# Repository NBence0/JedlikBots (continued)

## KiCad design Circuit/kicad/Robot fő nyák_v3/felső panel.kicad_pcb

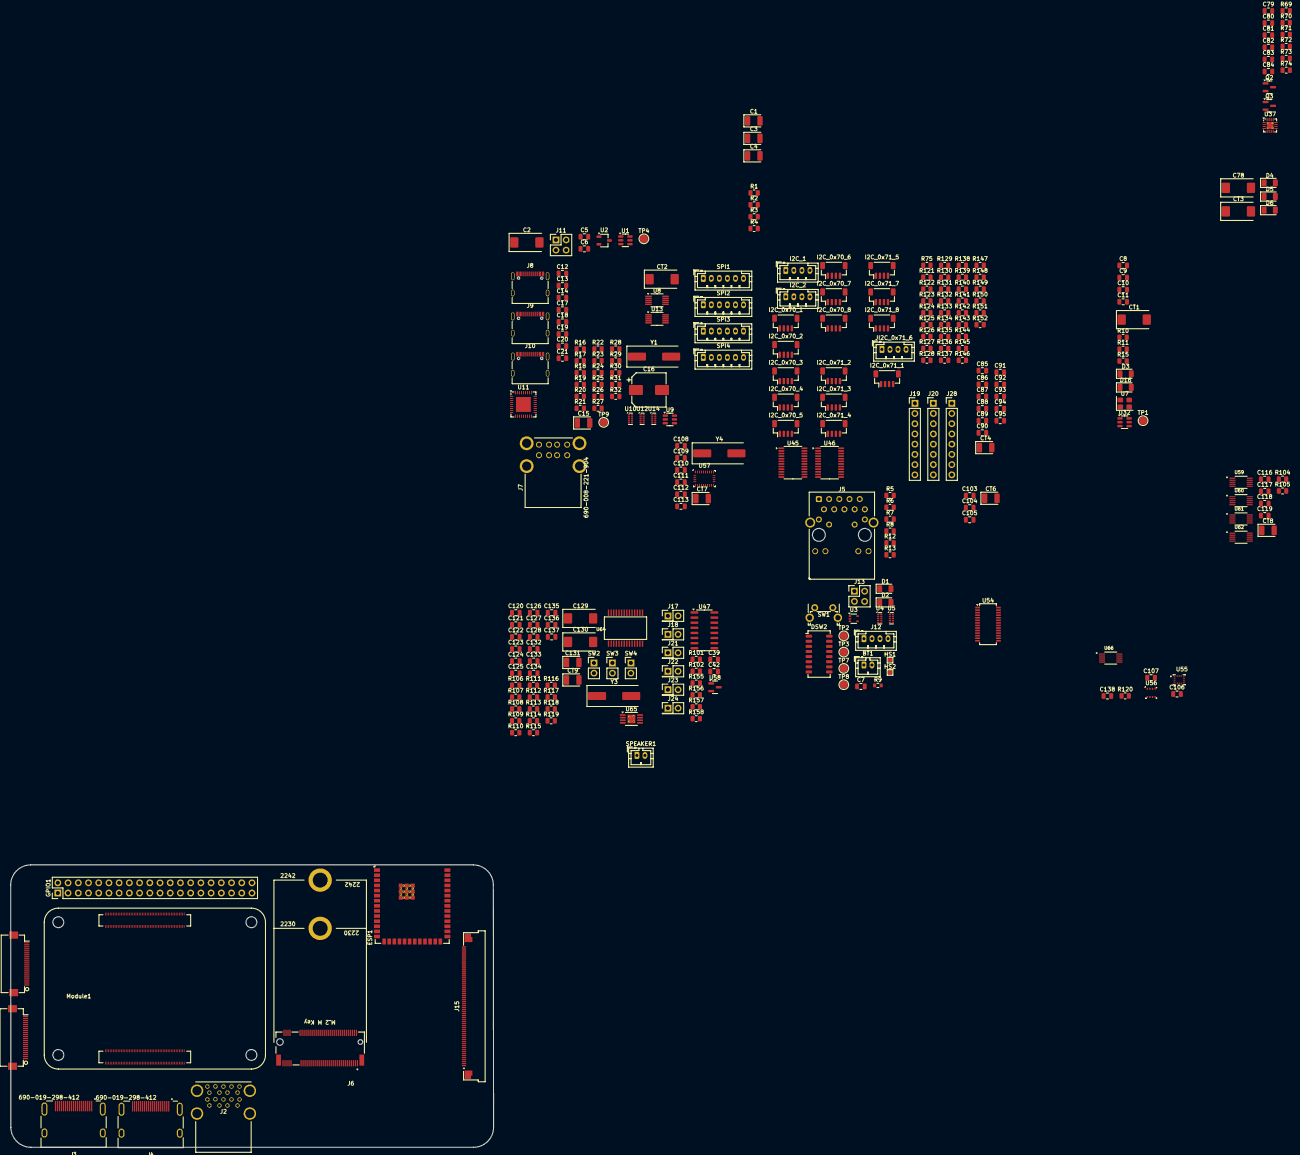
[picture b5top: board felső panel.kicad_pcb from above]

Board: 6 copper layers, 120.0 x 70.2 mm, 283 parts (0 on the bottom side), 343 nets, no tracks yet.

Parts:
BT1: Battery_Cell; JST_PH_B2B-PH-K_1x02_P2.00mm_Vertical
C1, C3, C4, C15: 10u; CP_EIA-3528-21_Kemet-B
C2: 100uF; CP_EIA-7343-31_Kemet-D
C5, C6, C7, C11: 100n; C_0805_2012Metric
C8, C9, C10, C17, C18, C19, C20, C21, C80, C81, C82, C83, C85, C86, C87, C88, C89, C90, C91, C92, C93, C94, C95, C103, C104, C105, C106, C107, C110, C111, C116, C117, C118, C119, C121, C124, C125, C127, C128, C132, C133, C134, C135, C136, C138: 1uf; C_0805_2012Metric
C12, C14, C120, C122: 22pf; C_0805_2012Metric
C13, C42, C79, C84: 100nf; C_0805_2012Metric
C16: 470uF; CP_Elec_8x10
C39: 68pf; C_0805_2012Metric
C78, C129, C130: 100uf; CP_EIA-7343-31_Kemet-D
C108, C109: 0.1uF; C_0805_2012Metric
C112, C113: 22pF; C_0805_2012Metric
C123, C126, C137: 0.022-μF; C_0805_2012Metric
C131: 10uf; CP_EIA-3528-21_Kemet-B
CT1, CT2, CT3: 100uf; CP_EIA-7343-31_Kemet-D
CT4, CT6, CT7, CT8, CT9: 10uf; CP_EIA-3528-21_Kemet-B
D1, D3: LED Green; D_1206_3216Metric
D2: LED Red; D_1206_3216Metric
D4, D5, D6, D16: LED; D_1206_3216Metric
DSI1, DSI2: Conn_01x22_Female; Hirose_FH12-22S-0.5SH_1x22-1MP_P0.50mm_Horizontal
DSW2: SW_DIP_x08; SW_DIP_SPSTx08_Slide_Copal_CHS-08A_W5.08mm_P1.27mm_JPin
ESP1: ESP32-S3-WROOM-2
GPIO1: THD-20-R; PinHeader_2x20_P2.54mm_Vertical
HS1, HS2: Heatsink; TestPoint_Pad_1.0x1.0mm
I2C_0x70_1, I2C_0x70_2, I2C_0x70_3, I2C_0x70_4, I2C_0x70_5, I2C_0x70_6, I2C_0x70_7, I2C_0x70_8, I2C_0x71_1, I2C_0x71_2, I2C_0x71_3, I2C_0x71_4, I2C_0x71_5, I2C_0x71_7, I2C_0x71_8: Conn_01x04_Pin; JST_SH_BM04B-SRSS-TB_1x04-1MP_P1.00mm_Vertical
I2C_1, I2C_2: Conn_01x04_Pin; JST_PH_B4B-PH-K_1x04_P2.00mm_Vertical
J2: USB3_A; MTCONN_UBAF30-D2011
J3, J4: 690-019-298-412; EDAC 690-019-298-412
J5: MagJack-A70-112-331N126; TRJG0926HENL
J6: Bus_M.2_Socket_M; M.2 M Key socket
J7: 690-008-221-904; MOLEX_USB_67298-4090
J8, J9, J10: USB_C_Receptacle_USB2.0_16P; USB_C_Receptacle_Palconn_UTC16-G
J11, J13: THD-02-R; PinHeader_2x02_P2.54mm_Vertical
J12: Conn_01x04_Socket; JST_PH_B4B-PH-K_1x04_P2.00mm_Vertical
J15: Conn_01x60_MountingPin; Amphenol_F32Q-1A7x1-11060_1x60-1MP_P0.5mm_Horizontal
J17, J18, J21, J22, J23, J24: Conn_01x02_Pin; PinHeader_2x01_P2.54mm_Vertical
J19, J20, J28: Conn_01x08_Pin; PinHeader_1x08_P2.54mm_Vertical
JI2C_0x71_6: Conn_01x04_Pin; JST_PH_B4B-PH-K_1x04_P2.00mm_Vertical
Module1: ComputeModule5-CM5; Raspberry-Pi-5-Compute-Module
Q2, Q3: bc akármi; SOT-23
R1, R26: 15K 1%; R_0805_2012Metric
R2, R3, R4, R16, R17, R27, R28, R121, R122, R123, R124, R125, R126, R127, R128, R129, R130, R131, R132, R133, R134, R135, R136, R137, R138, R139, R140, R141, R142, R143, R144, R145, R146, R147, R148, R149, R150, R151, R152: 2.2K 1%; R_0805_2012Metric
R5, R6, R7: 4.7k; R_0805_2012Metric
R8, R15, R69, R70, R71: 1k; R_0805_2012Metric
R9: 1k; R_0603_1608Metric
R10, R18, R72, R73, R74, R75, R101, R102, R155, R156, R157, R158: 10k; R_0805_2012Metric
R11: 100; R_0805_2012Metric
R12, R13: 470R; R_0805_2012Metric
R19, R20, R21, R25: 36K 1%; R_0805_2012Metric
R22: 12K 1%; R_0805_2012Metric
R23, R24, R29, R30, R31, R32: 5.1K 1%; R_0805_2012Metric
R104, R105, R120: 47k; R_0805_2012Metric
R106, R107: 1.5-kΩ; R_0805_2012Metric
R108: 22; R_0805_2012Metric
R109: 22Ω; R_0805_2012Metric
R110: 1M; R_0805_2012Metric
R111, R112: 16; R_0805_2012Metric
R113, R114: 330; R_0805_2012Metric
R115, R116, R117, R118, R119: 10K; R_0805_2012Metric
SPEAKER1: Conn_01x02_Pin; JST_PH_B2B-PH-K_1x02_P2.00mm_Vertical
SPI1, SPI2, SPI3, SPI4: Conn_01x06_Socket; JST_PH_B6B-PH-K_1x06_P2.00mm_Vertical
SW1: Right angle Tact button; SW_Tactile_SPST_Angled_PTS645Vx58-2LFS
SW2, SW3, SW4: SW_Push; PinHeader_1x02_P2.54mm_Vertical
TP1, TP2, TP3, TP4, TP7, TP8, TP9: TestPoint; TestPoint_Pad_D2.0mm
U1, U9: AP22653W6; SOT-23-6
U2: RT9742SNGV; TSOT-23
U3: 74LVC1G07SE-7; SOT-353_SC-70-5
U4, U5, U10, U12, U14: TPD4EUSB30; USON-10_2.5x1.0mm_P0.5mm
U7: ASEK-32.768KHZ-L-R-T; Crystal_SMD_3225-4Pin_3.2x2.5mm
U8, U13: FSUSB42MUX; MSOP-10_3x3mm_P0.5mm
U11: USB2514B-I/M2; QFN-36-1EP_6x6mm_P0.5mm_EP3.7x3.7mm
U32: AP22815AWU; SOT-23-6
U37: CH343P; QFN-16-1EP_3x3mm_P0.5mm_EP1.7x1.7mm_ThermalVias
U45, U46: TCA9548APWR; TSSOP-24_4.4x7.8mm_P0.65mm
U47: MCP3208; SOIC-16_3.9x9.9mm_P1.27mm
U54: MCP23S17_SO; SSOP-28_3.9x9.9mm_P0.635mm
U55: ICM-45686; IC_ICM-45686
U56: BME280; Bosch_LGA-8_2.5x2.5mm_P0.65mm_ClockwisePinNumbering
U57: BNO080; LGA-28_5.2x3.8mm_P0.5mm
U58: MCP1541-TT; SOT-23
U59, U60, U61, U62, U66: TS5A23157DGSR; SOP50P490X110-10N
U64: PCM2704CDBR; SSOP28
U65: TPA6203A1DGN; MSOP-8-1EP_3x3mm_P0.65mm_EP1.95x2.15mm_ThermalVias
Y1: 24MHz; Crystal_SMD_HC49-SD
Y3: 5MHz; Crystal_SMD_HC49-SD
Y4: 32.768MHz; Crystal_SMD_HC49-SD

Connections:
1.8V: J20.7, J20.8, Module1.88 (+1.8v_(Output)), Module1.90 (+1.8v_(Output)), TP8.1
3V3_M.2: GPIO1.1, GPIO1.17, J15.38, J15.39, J15.40, J15.41, J15.42, J15.43, R10.1, R11.1, U32.6 (IN)
5V1: C1.1, C5.1, C15.1, C121.2, C134.1, C135.1, C136.1, CT9.1, J15.55, J15.56, U1.1 (IN), U2.1 (IN), U9.1 (IN), U64.10 (VBUS), U65.6 (V_{DD})
/CM5_GPIO ( Ethernet, GPIO, SDCARD)/+3.3v: D1.2 (A), D2.2 (A), DSI1.22, DSI2.22, J5.15 (LEDY_A), J5.17 (LEDG_A), Module1.78 (GPIO_VREF(1.8v/3.3v_Input)), Module1.84 (+3.3v_(Output)), Module1.86 (+3.3v_(Output)), R2.1, TP7.1, U3.5 (VCC)
/CM5_GPIO ( Ethernet, GPIO, SDCARD)/CAM_GPIO0: DSI1.17, Module1.97 (CAM_GPIO0)
/CM5_GPIO ( Ethernet, GPIO, SDCARD)/CAM_GPIO1: DSI1.18, Module1.100 (CAM_GPIO1)
/CM5_GPIO ( Ethernet, GPIO, SDCARD)/ETH_LEDG: Module1.17 (Ethernet_nLED2(3.3v)), R12.2
/CM5_GPIO ( Ethernet, GPIO, SDCARD)/ETH_LEDY: Module1.15 (Ethernet_nLED3(3.3v)), R13.2
/CM5_GPIO ( Ethernet, GPIO, SDCARD)/GPIO2: GPIO1.3, Module1.58 (GPIO2)
/CM5_GPIO ( Ethernet, GPIO, SDCARD)/GPIO3: GPIO1.5, Module1.56 (GPIO3)
/CM5_GPIO ( Ethernet, GPIO, SDCARD)/GPIO12: GPIO1.32, Module1.31 (GPIO12)
/CM5_GPIO ( Ethernet, GPIO, SDCARD)/GPIO13: GPIO1.33, Module1.28 (GPIO13)
/CM5_GPIO ( Ethernet, GPIO, SDCARD)/GPIO16: GPIO1.36, Module1.29 (GPIO16)
/CM5_GPIO ( Ethernet, GPIO, SDCARD)/GPIO17: GPIO1.11, Module1.50 (GPIO17)
/CM5_GPIO ( Ethernet, GPIO, SDCARD)/GPIO18: GPIO1.12, Module1.49 (GPIO18)
/CM5_GPIO ( Ethernet, GPIO, SDCARD)/GPIO22: GPIO1.15, Module1.46 (GPIO22)
/CM5_GPIO ( Ethernet, GPIO, SDCARD)/GPIO23: GPIO1.16, Module1.47 (GPIO23)
/CM5_GPIO ( Ethernet, GPIO, SDCARD)/GPIO24: GPIO1.18, Module1.45 (GPIO24)
/CM5_GPIO ( Ethernet, GPIO, SDCARD)/GPIO25: GPIO1.22, Module1.41 (GPIO25)
/CM5_GPIO ( Ethernet, GPIO, SDCARD)/GPIO26: GPIO1.37, Module1.24 (GPIO26)
/CM5_GPIO ( Ethernet, GPIO, SDCARD)/GPIO27: GPIO1.13, Module1.48 (GPIO27)
/CM5_GPIO ( Ethernet, GPIO, SDCARD)/ID_SC: GPIO1.28, J11.1, Module1.35 (ID_SC)
/CM5_GPIO ( Ethernet, GPIO, SDCARD)/ID_SD: GPIO1.27, J11.3, Module1.36 (ID_SD)
/CM5_GPIO ( Ethernet, GPIO, SDCARD)/PWM: J12.2, Module1.19 (FAN_PWM)
/CM5_GPIO ( Ethernet, GPIO, SDCARD)/PWR_BUT: Module1.92 (PWR_BUT), SW1.1
/CM5_GPIO ( Ethernet, GPIO, SDCARD)/SYNC_OUT: Module1.18 (Ethernet_SYNC_OUT(3.3v)), TP2.1
/CM5_GPIO ( Ethernet, GPIO, SDCARD)/TACHO: J12.4, Module1.16 (FAN_TACHO)
/CM5_GPIO ( Ethernet, GPIO, SDCARD)/TR0_TAP: J5.11 (VC1), J13.3
/CM5_GPIO ( Ethernet, GPIO, SDCARD)/TR1_TAP: J5.12 (VC2), J13.1
/CM5_GPIO ( Ethernet, GPIO, SDCARD)/TR2_TAP: J5.13 (VC3), J13.2
/CM5_GPIO ( Ethernet, GPIO, SDCARD)/TR3_TAP: J5.14 (VC4), J13.4
/CM5_GPIO ( Ethernet, GPIO, SDCARD)/TRD0_N: J5.2 (TRD0-), Module1.10 (Ethernet_Pair0_N), U5.4 (D2+), U5.7
/CM5_GPIO ( Ethernet, GPIO, SDCARD)/TRD0_P: J5.1 (TRD0+), Module1.12 (Ethernet_Pair0_P), U5.5 (D2-), U5.6
/CM5_GPIO ( Ethernet, GPIO, SDCARD)/TRD1_N: J5.6 (TRD1-), Module1.6 (Ethernet_Pair1_N), U5.2 (D1-), U5.9
/CM5_GPIO ( Ethernet, GPIO, SDCARD)/TRD1_P: J5.3 (TRD1+), Module1.4 (Ethernet_Pair1_P), U5.1 (D1+), U5.10
/CM5_GPIO ( Ethernet, GPIO, SDCARD)/TRD2_N: J5.8 (TRD2-), Module1.9 (Ethernet_Pair2_N), U4.4 (D2+), U4.7
/CM5_GPIO ( Ethernet, GPIO, SDCARD)/TRD2_P: J5.7 (TRD2+), Module1.11 (Ethernet_Pair2_P), U4.5 (D2-), U4.6
/CM5_GPIO ( Ethernet, GPIO, SDCARD)/TRD3_N: J5.10 (TRD3-), Module1.5 (Ethernet_Pair3_N), U4.2 (D1-), U4.9
/CM5_GPIO ( Ethernet, GPIO, SDCARD)/TRD3_P: J5.9 (TRD3+), Module1.3 (Ethernet_Pair3_P), U4.1 (D1+), U4.10
/CM5_GPIO ( Ethernet, GPIO, SDCARD)/VBAT: BT1.1 (+), Module1.76 (VBAT)
/CM5_GPIO ( Ethernet, GPIO, SDCARD)/nPWR_LED: Module1.95 (LED_nPWR), U3.2
/CM5_HighSpeed/DPHY0_C_N: DSI1.8, Module1.127 (MIPI0_C_N)
/CM5_HighSpeed/DPHY0_C_P: DSI1.9, Module1.129 (MIPI0_C_P)
/CM5_HighSpeed/DPHY0_D0_N: DSI1.2, Module1.115 (MIPI0_D0_N)
/CM5_HighSpeed/DPHY0_D0_P: DSI1.3, Module1.117 (MIPI0_D0_P)
/CM5_HighSpeed/DPHY0_D1_N: DSI1.5, Module1.121 (MIPI0_D1_N)
/CM5_HighSpeed/DPHY0_D1_P: DSI1.6, Module1.123 (MIPI0_D1_P)
/CM5_HighSpeed/DPHY0_D2_N: DSI1.11, Module1.133 (MIPI0_D2_N)
/CM5_HighSpeed/DPHY0_D2_P: DSI1.12, Module1.135 (MIPI0_D2_P)
/CM5_HighSpeed/DPHY0_D3_N: DSI1.14, Module1.139 (MIPI0_D3_N)
/CM5_HighSpeed/DPHY0_D3_P: DSI1.15, Module1.141 (MIPI0_D3_P)
/CM5_HighSpeed/DPHY1_C_N: DSI2.8, Module1.187 (MIPI1_C_N)
/CM5_HighSpeed/DPHY1_C_P: DSI2.9, Module1.189 (MIPI1_C_P)
/CM5_HighSpeed/DPHY1_D0_N: DSI2.2, Module1.175 (MIPI1_D0_N)
/CM5_HighSpeed/DPHY1_D0_P: DSI2.3, Module1.177 (MIPI1_D0_P)
/CM5_HighSpeed/DPHY1_D1_N: DSI2.5, Module1.181 (MIPI1_D1_N)
/CM5_HighSpeed/DPHY1_D1_P: DSI2.6, Module1.183 (MIPI1_D1_P)
/CM5_HighSpeed/DPHY1_D2_N: DSI2.11, Module1.193 (MIPI1_D2_N)
/CM5_HighSpeed/DPHY1_D2_P: DSI2.12, Module1.195 (MIPI1_D2_P)
/CM5_HighSpeed/DPHY1_D3_N: DSI2.14, Module1.194 (MIPI1_D3_N)
/CM5_HighSpeed/DPHY1_D3_P: DSI2.15, Module1.196 (MIPI1_D3_P)
/CM5_HighSpeed/GPIO_VREF: R3.1, R4.1
/CM5_HighSpeed/HDMI0_CEC: J3.13 (CEC), Module1.151 (HDMI0_CEC)
/CM5_HighSpeed/HDMI0_CK_N: J3.12 (CK-), Module1.190 (HDMI0_CLK_N)
/CM5_HighSpeed/HDMI0_CK_P: J3.10 (CK+), Module1.188 (HDMI0_CLK_P)
/CM5_HighSpeed/HDMI0_D0_N: J3.9 (D0-), Module1.184 (HDMI0_TX0_N)
/CM5_HighSpeed/HDMI0_D0_P: J3.7 (D0+), Module1.182 (HDMI0_TX0_P)
/CM5_HighSpeed/HDMI0_D1_N: J3.6 (D1-), Module1.178 (HDMI0_TX1_N)
/CM5_HighSpeed/HDMI0_D1_P: J3.4 (D1+), Module1.176 (HDMI0_TX1_P)
/CM5_HighSpeed/HDMI0_D2_N: J3.3 (D2-), Module1.172 (HDMI0_TX2_N)
/CM5_HighSpeed/HDMI0_D2_P: J3.1 (D2+), Module1.170 (HDMI0_TX2_P)
/CM5_HighSpeed/HDMI0_HOTPLUG: J3.19 (HPD/HEAC-), Module1.153 (HDMI0_HOTPLUG)
/CM5_HighSpeed/HDMI0_SCL: J3.15 (SCL), Module1.200 (HDMI0_SCL)
/CM5_HighSpeed/HDMI0_SDA: J3.16 (SDA), Module1.199 (HDMI0_SDA)
/CM5_HighSpeed/HDMI1_CEC: J4.13 (CEC), Module1.149 (HDMI1_CEC)
/CM5_HighSpeed/HDMI1_CK_N: J4.12 (CK-), Module1.166 (HDMI1_CLK_N)
/CM5_HighSpeed/HDMI1_CK_P: J4.10 (CK+), Module1.164 (HDMI1_CLK_P)
/CM5_HighSpeed/HDMI1_D0_N: J4.9 (D0-), Module1.160 (HDMI1_TX0_N)
/CM5_HighSpeed/HDMI1_D0_P: J4.7 (D0+), Module1.158 (HDMI1_TX0_P)
/CM5_HighSpeed/HDMI1_D1_N: J4.6 (D1-), Module1.154 (HDMI1_TX1_N)
/CM5_HighSpeed/HDMI1_D1_P: J4.4 (D1+), Module1.152 (HDMI1_TX1_P)
/CM5_HighSpeed/HDMI1_D2_N: J4.3 (D2-), Module1.148 (HDMI1_TX2_N)
/CM5_HighSpeed/HDMI1_D2_P: J4.1 (D2+), Module1.146 (HDMI1_TX2_P)
/CM5_HighSpeed/HDMI1_HOTPLUG: J4.19 (HPD/HEAC-), Module1.143 (HDMI1_HOTPLUG)
/CM5_HighSpeed/HDMI1_SCL: J4.15 (SCL), Module1.147 (HDMI1_SCL)
/CM5_HighSpeed/HDMI1_SDA: J4.16 (SDA), Module1.145 (HDMI1_SDA)
/CM5_HighSpeed/HDMI_5v: C6.1, J3.18 (+5V), J4.18 (+5V), U2.2 (OUT)
/CM5_HighSpeed/PCIE_CLK_N: J6.53 (REFCLKn), Module1.112 (PCIe_CLK_N)
/CM5_HighSpeed/PCIE_CLK_P: J6.55 (REFCLKp), Module1.110 (PCIe_CLK_P)
/CM5_HighSpeed/PCIE_PWR_EN: Module1.106 (PCIE_PWR_EN), U32.4 (EN)
/CM5_HighSpeed/PCIE_RX_N: J6.43 (PETp0), Module1.118 (PCIe_RX_N)
/CM5_HighSpeed/PCIE_RX_P: J6.41 (PETn0), Module1.116 (PCIe_RX_P)
/CM5_HighSpeed/PCIE_TX_N: J6.49 (PERp0), Module1.124 (PCIe_TX_N)
/CM5_HighSpeed/PCIE_TX_P: J6.47 (PERn0), Module1.122 (PCIe_TX_P)
/CM5_HighSpeed/PCIE_nCLKREQ: J6.52 (~CLKREQ), Module1.102 (PCIe_nCLKREQ)
/CM5_HighSpeed/PCIE_nRST: J6.50 (~PERST), Module1.109 (PCIe_nRST)
/CM5_HighSpeed/PCIE_nWAKE: J6.54 (~PEWAKE), Module1.104 (PCIE_nWAKE)
/CM5_HighSpeed/SCL0: DSI1.20, Module1.80 (SCL0)
/CM5_HighSpeed/SCL1: DSI2.20, J11.2, R4.2
/CM5_HighSpeed/SDA0: DSI1.21, Module1.82 (SDA0)
/CM5_HighSpeed/SDA1: DSI2.21, J11.4, R3.2
/CM5_HighSpeed/USB2_N: Module1.103 (USB2_N), U8.4 (D_N)
/CM5_HighSpeed/USB2_P: Module1.105 (USB2_P), U8.3 (D_P)
/CM5_HighSpeed/USB3-0-D_N: J2.A2 (D-), Module1.136 (USB3-0-D_N)
/CM5_HighSpeed/USB3-0-D_P: J2.A3 (D+), Module1.134 (USB3-0-D_P)
/CM5_HighSpeed/USB3-0-RX_N: J2.A6 (SSRX+), Module1.128 (USB3-0-RX_N)
/CM5_HighSpeed/USB3-0-RX_P: J2.A5 (SSRX-), Module1.130 (USB3-0-RX_P)
/CM5_HighSpeed/USB3-0-TX_N: J2.A9 (SSTX+), Module1.140 (USB3-0-TX_N)
/CM5_HighSpeed/USB3-0-TX_P: J2.A8 (SSTX-), Module1.142 (USB3-0-TX_P)
/CM5_HighSpeed/USB3-1-D_N: J2.B2 (D-), Module1.165 (USB3-1-D_N)
/CM5_HighSpeed/USB3-1-D_P: J2.B3 (D+), Module1.163 (USB3-1-D_P)
/CM5_HighSpeed/USB3-1-RX_N: J2.B6 (SSRX+), Module1.157 (USB3-1-RX_N)
/CM5_HighSpeed/USB3-1-RX_P: J2.B5 (SSRX-), Module1.159 (USB3-1-RX_P)
/CM5_HighSpeed/USB3-1-TX_N: J2.B9 (SSTX+), Module1.169 (USB3-1-TX_N)
/CM5_HighSpeed/USB3-1-TX_P: J2.B8 (SSTX-), Module1.171 (USB3-1-TX_P)
/CM5_HighSpeed/USBOTG_ID: Module1.101 (USB_OTG_ID), R16.1, R17.2, U8.2 (SEL)
/CM5_HighSpeed/VBUS: C2.1, C3.1, C4.1, J2.A1 (VBUS), J2.B1 (VBUS), TP4.1, U1.6 (OUT)
/CM5_HighSpeed/VBUS_EN: Module1.111 (VBUS_EN), U1.3 (EN)
/PCIe-M2/M2_3v3: C8.1, C9.1, C10.1, C11.1, CT1.1, D3.2 (A), J6.2 (3.3V), J6.4 (3.3V), J6.12 (3.3V), J6.14 (3.3V), J6.16 (3.3V), J6.18 (3.3V), J6.70 (3.3V), J6.72 (3.3V), J6.74 (3.3V), TP1.1, U7.1 (EN), U7.4 (VDD), U32.1 (OUT)
/USB2-HUB/CH343P_usbD+: U13.3 (D_P), U37.7 (UD+)
/USB2-HUB/CH343P_usbD-: U13.4 (D_N), U37.8 (UD-)
/USB2-HUB/ESP_usbD+: ESP1.14 (USB_D+/IO20), J9.A6 (D+), J9.B6 (D+), U14.4 (D2+), U14.7
/USB2-HUB/ESP_usbD-: ESP1.13 (USB_D-/IO19), J9.A7 (D-), J9.B7 (D-), U14.5 (D2-), U14.6
/USB2-HUB/HD1_N: J7.2 (D-`), U11.1 (USBDM_DN1/PRT_DIS_M1), U12.5 (D2-), U12.6
/USB2-HUB/HD1_P: J7.3 (D+`), U11.2 (USBDP_DN1/PRT_DIS_P1), U12.4 (D2+), U12.7
/USB2-HUB/HD2_N: J7.6 (D-), U11.3 (USBDM_DN2/PRT_DIS_M2), U12.2 (D1-), U12.9
/USB2-HUB/HD2_P: J7.7 (D+), U11.4 (USBDP_DN2/PRT_DIS_P2), U12.1 (D1+), U12.10
/USB2-HUB/HD3_N: U11.6 (USBDM_DN3/PRT_DIS_M3), U13.6 (HSD0_M)
/USB2-HUB/HD3_P: U11.7 (USBDP_DN3/PRT_DIS_P3), U13.7 (HSD0_P)
/USB2-HUB/HD4_N: R109.1, U11.8 (USBDM_DN4/PRT_DIS_M4)
/USB2-HUB/HD4_P: R107.2, R108.1, U11.9 (USBDP_DN4/PRT_DIS_P4)
/USB2-HUB/PWR1: U9.3 (EN), U11.12 (PRTPWR1/BC_EN1)
/USB2-HUB/USBD_N: J8.A6 (D+), J8.B6 (D+), U8.8 (HSD1_M), U10.2 (D1-), U10.9
/USB2-HUB/USBD_P: J8.A7 (D-), J8.B7 (D-), U8.9 (HSD1_P), U10.1 (D1+), U10.10
/USB2-HUB/USBH_N: U8.6 (HSD0_M), U11.30 (USBDM_UP)
/USB2-HUB/USBH_P: U8.7 (HSD0_P), U11.31 (USBDP_UP)
/USB2-HUB/USB_AUDIO/BYPASS: C137.1, U65.2 (BYPASS)
/USB2-HUB/USB_AUDIO/Vdd: C124.1, R106.2, R107.1, U64.4 (PSEL), U64.7 (VDD), U64.21 (HOST), U64.25 (TEST1), U64.26 (TEST0)
/USB2-HUB/VBUS: C16.1, J7.1 (VBUS`), J7.5 (VBUS), TP9.1, U9.6 (OUT)
/USB2-HUB/nEXTRST: C13.2, J8.A4 (VBUS), J8.A9 (VBUS), J8.B4 (VBUS), J8.B9 (VBUS), R17.1, R18.1
/USB2-HUB/nOCS1: U9.4 (nFault), U11.13 (OCS_N1), U11.17 (OCS_N2), U11.19 (OCS_N3), U11.21 (OCS_N4)
/YD-ESP32-S3/CS1: U54.1 (GPB0), U56.2 (CSB)
/YD-ESP32-S3/CS2: U54.2 (GPB1), U57.18 (H_CSN)
/YD-ESP32-S3/CS3: U54.3 (GPB2), U55.12 (AP_CS)
/YD-ESP32-S3/CS4: U47.10 (~CS/SHDN), U54.4 (GPB3)
/YD-ESP32-S3/CS5: SPI4.5, U54.5 (GPB4)
/YD-ESP32-S3/CS6: SPI3.5, U54.6 (GPB5)
/YD-ESP32-S3/CS7: SPI2.5, U54.7 (GPB6)
/YD-ESP32-S3/CS8: SPI1.5, U54.8 (GPB7)
/YD-ESP32-S3/I2C_MUX/ESP_I2C_SCL_sensors: ESP1.35 (MTMS/IO42), U66.7 (NC2)
/YD-ESP32-S3/I2C_MUX/ESP_I2C_SDA_sensors: ESP1.34 (MTDI/IO41), U66.9 (NC1)
/YD-ESP32-S3/I2C_SCL_sensors: I2C_1.2, I2C_2.2, J15.10, U45.23 (SDA), U46.23 (SDA), U66.10 (COM1)
/YD-ESP32-S3/I2C_SDA_sensors: I2C_1.3, I2C_2.3, J15.9, U45.22 (SCL), U46.22 (SCL), U66.6 (COM2)
/YD-ESP32-S3/I2C_devices/SCL1: I2C_0x71_1.3, R137.2, U45.5 (SC0)
/YD-ESP32-S3/I2C_devices/SCL2: I2C_0x71_2.3, R139.2, U45.7 (SC1)
/YD-ESP32-S3/I2C_devices/SCL2_1: I2C_0x70_1.3, R129.2, U46.5 (SC0)
/YD-ESP32-S3/I2C_devices/SCL2_2: I2C_0x70_2.3, R131.2, U46.7 (SC1)
/YD-ESP32-S3/I2C_devices/SCL2_3: I2C_0x70_3.3, R133.2, U46.9 (SC2)
/YD-ESP32-S3/I2C_devices/SCL2_4: I2C_0x70_4.3, R135.2, U46.11 (SC3)
/YD-ESP32-S3/I2C_devices/SCL2_5: I2C_0x70_5.3, R125.2, U46.14 (SC4)
/YD-ESP32-S3/I2C_devices/SCL2_6: I2C_0x70_6.3, R127.2, U46.16 (SC5)
/YD-ESP32-S3/I2C_devices/SCL2_7: I2C_0x70_7.3, R123.2, U46.18 (SC6)
/YD-ESP32-S3/I2C_devices/SCL2_8: I2C_0x70_8.3, R122.2, U46.20 (SC7)
/YD-ESP32-S3/I2C_devices/SCL3: I2C_0x71_3.3, R141.2, U45.9 (SC2)
/YD-ESP32-S3/I2C_devices/SCL4: I2C_0x71_4.3, R143.2, U45.11 (SC3)
/YD-ESP32-S3/I2C_devices/SCL5: I2C_0x71_5.3, R145.2, U45.14 (SC4)
/YD-ESP32-S3/I2C_devices/SCL6: JI2C_0x71_6.3, R147.2, U45.16 (SC5)
/YD-ESP32-S3/I2C_devices/SCL7: I2C_0x71_7.3, R149.2, U45.18 (SC6)
/YD-ESP32-S3/I2C_devices/SCL8: I2C_0x71_8.3, R151.2, U45.20 (SC7)
/YD-ESP32-S3/I2C_devices/SDA1: I2C_0x71_1.2, R138.2, U45.4 (SD0)
/YD-ESP32-S3/I2C_devices/SDA2: I2C_0x71_2.2, R140.2, U45.6 (SD1)
/YD-ESP32-S3/I2C_devices/SDA2_1: I2C_0x70_1.2, R130.2, U46.4 (SD0)
/YD-ESP32-S3/I2C_devices/SDA2_2: I2C_0x70_2.2, R132.2, U46.6 (SD1)
/YD-ESP32-S3/I2C_devices/SDA2_3: I2C_0x70_3.2, R134.2, U46.8 (SD2)
/YD-ESP32-S3/I2C_devices/SDA2_4: I2C_0x70_4.2, R136.2, U46.10 (SD3)
/YD-ESP32-S3/I2C_devices/SDA2_5: I2C_0x70_5.2, R126.2, U46.13 (SD4)
/YD-ESP32-S3/I2C_devices/SDA2_6: I2C_0x70_6.2, R128.2, U46.15 (SD5)
/YD-ESP32-S3/I2C_devices/SDA2_7: I2C_0x70_7.2, R124.2, U46.17 (SD6)
/YD-ESP32-S3/I2C_devices/SDA2_8: I2C_0x70_8.2, R121.2, U46.19 (SD7)
/YD-ESP32-S3/I2C_devices/SDA3: I2C_0x71_3.2, R142.2, U45.8 (SD2)
/YD-ESP32-S3/I2C_devices/SDA4: I2C_0x71_4.2, R144.2, U45.10 (SD3)
/YD-ESP32-S3/I2C_devices/SDA5: I2C_0x71_5.2, R146.2, U45.13 (SD4)
/YD-ESP32-S3/I2C_devices/SDA6: JI2C_0x71_6.2, R148.2, U45.15 (SD5)
/YD-ESP32-S3/I2C_devices/SDA7: I2C_0x71_7.2, R150.2, U45.17 (SD6)
/YD-ESP32-S3/I2C_devices/SDA8: I2C_0x71_8.2, R152.2, U45.19 (SD7)
/YD-ESP32-S3/I2C_devices/output_pin_1: C85.1, I2C_0x71_1.1, I2C_0x71_2.1, J19.1
/YD-ESP32-S3/I2C_devices/output_pin_2: C86.1, I2C_0x71_3.1, I2C_0x71_4.1, J19.2
/YD-ESP32-S3/I2C_devices/output_pin_3: C87.1, I2C_0x71_5.1, J19.3, JI2C_0x71_6.1
/YD-ESP32-S3/I2C_devices/output_pin_4: C88.1, I2C_0x71_7.1, I2C_0x71_8.1, J19.4
/YD-ESP32-S3/I2C_devices/output_pin_5: C89.1, I2C_0x70_1.1, I2C_0x70_2.1, J19.5
/YD-ESP32-S3/I2C_devices/output_pin_6: C90.1, I2C_0x70_3.1, I2C_0x70_4.1, J19.6
/YD-ESP32-S3/I2C_devices/output_pin_7: C91.1, I2C_0x70_5.1, I2C_0x70_6.1, J19.7
/YD-ESP32-S3/I2C_devices/output_pin_8: C92.1, I2C_0x70_7.1, I2C_0x70_8.1, J19.8
/YD-ESP32-S3/M1_step: ESP1.39 (IO1), J15.17
/YD-ESP32-S3/M2_step: ESP1.38 (IO2), J15.16
/YD-ESP32-S3/M3_step: ESP1.15 (IO3), J15.15
/YD-ESP32-S3/M4_step: ESP1.4 (IO4), J15.14
/YD-ESP32-S3/MCP_RST: ESP1.6 (IO6), J15.20, U54.18 (~RESET)
/YD-ESP32-S3/PWMA: ESP1.7 (IO7), J15.19
/YD-ESP32-S3/PWMB: ESP1.12 (IO8), J15.18
/YD-ESP32-S3/SPI_2_CLK: J15.7, SPI1.2, SPI2.2, SPI3.2, SPI4.2, U47.13 (CLK), U54.12 (SCK), U55.13 (AP_SCL/AP_SCLK), U56.4 (SCK), U57.19 (H_SCL/SCLK/RX), U61.10 (COM1)
/YD-ESP32-S3/SPI_2_MISO: J15.5, SPI1.3, SPI2.3, SPI3.3, SPI4.3, U47.12 (Dout), U54.14 (SO), U55.1 (AP_SDO/AP_AD0), U56.5 (SDO), U57.20 (H_SDA/MISO/TX), U62.6 (COM2)
/YD-ESP32-S3/SPI_2_MOSI: J15.6, SPI1.4, SPI2.4, SPI3.4, SPI4.4, U47.11 (Din), U54.13 (SI), U55.14 (AP_SDA/AP_SDIO/AP_SDI), U56.3 (SDI), U57.17 (H_SA0/MOSI), U62.10 (COM1)
/YD-ESP32-S3/SPI_devices/ADS8688/5v: R101.1, R102.1, R155.1, R156.1, R157.1, R158.1, U47.16 (Vdd), U58.1 (Vin)
/YD-ESP32-S3/SPI_devices/BMO085/3V3: C108.1, U57.3 (VDD), U57.5 (PS1), U57.6 (PS0/WAKE), U57.28 (VDDIO)
/YD-ESP32-S3/SPI_devices/BMO085/CAP: C109.2, U57.9 (CAP)
/YD-ESP32-S3/SPI_devices/BMO085/XIN: C112.1, U57.27 (XIN32), Y4.1
/YD-ESP32-S3/SPI_devices/BMO085/XOUT: C113.1, U57.26 (CLKSEL1/XOUT32), Y4.2
/YD-ESP32-S3/TMC_MISO: J15.2, U60.6 (COM2)
/YD-ESP32-S3/TMC_MOSI: J15.4, U60.10 (COM1)
/YD-ESP32-S3/TMC_SPI_CLK: J15.3, U59.10 (COM1)
/YD-ESP32-S3/esp32_chip_pu: C80.1, ESP1.3 (EN), Q3.3 (C), R72.1
/YD-ESP32-S3/esp32_gpio0: ESP1.27 (IO0), Q2.3 (C)
/YD-ESP32-S3/esp_rxd0: D6.1 (K), ESP1.37 (TXD0/IO43)
/YD-ESP32-S3/esp_txd0: D5.1 (K), ESP1.36 (RXD0/IO44), U37.4 (TXD), U37.5 (RXD)
/YD-ESP32-S3/spi_mux/ESP_MCP_CS: ESP1.5 (IO5), U61.7 (NC2)
/YD-ESP32-S3/spi_mux/ESP_SPI_2_CLK: ESP1.8 (IO15), U61.9 (NC1)
/YD-ESP32-S3/spi_mux/ESP_SPI_2_MISO: ESP1.9 (IO16), U62.7 (NC2)
/YD-ESP32-S3/spi_mux/ESP_SPI_2_MOSI: ESP1.22 (IO14), U62.9 (NC1)
/YD-ESP32-S3/spi_mux/ESP_TMC_MISO: ESP1.21 (IO13), U60.7 (NC2)
/YD-ESP32-S3/spi_mux/ESP_TMC_MOSI: ESP1.19 (IO11), U60.9 (NC1)
/YD-ESP32-S3/spi_mux/ESP_TMC_SPI_CLK: ESP1.20 (IO12), U59.9 (NC1)
B-B_2: J15.31, U54.23 (GPA2)
B-B_3: J15.30, U54.24 (GPA3)
B-B_4: J15.29, U54.25 (GPA4)
B-B_5: J15.28, U54.26 (GPA5)
B-B_6: J15.27, U54.27 (GPA6)
B-B_7: J15.26, U54.28 (GPA7)
BMO_INT: ESP1.17 (IO9), U57.14 (H_INTN)
EEPROM_nWP: DSW2.3, Module1.20 (EEPROM_nWP)
ESP_3v3: C17.1, C18.1, C19.1, C20.1, C21.1, C78.1, C79.1, C81.1, C82.1, C83.1, C103.1, C104.1, C105.1, C106.1, C107.1, C110.1, C111.1, C116.1, C117.1, C118.1, C119.1, C138.2, CT2.1, CT3.1, CT6.1, CT7.1, CT8.1, ESP1.2 (3V3), I2C_1.1, I2C_2.1, J15.36, J15.37, J20.1, J20.2, J20.3, J20.4, J20.5, J20.6, R69.2, R70.2, R71.2, R72.2, R121.1, R122.1, R123.1, R124.1, R125.1, R126.1, R127.1, R128.1, R129.1, R130.1, R131.1, R132.1, R133.1, R134.1, R135.1, R136.1, R137.1, R138.1, R139.1, R140.1, R141.1, R142.1, R143.1, R144.1, R145.1, R146.1, R147.1, R148.1, R149.1, R150.1, R151.1, R152.1, SPI1.1, SPI2.1, SPI3.1, SPI4.1, U8.1 (VCC), U11.5 (VDDA33), U11.10 (VDDA33), U11.15 (VDD33), U11.23 (VDD33), U11.27 (VBUS_DET), U11.29 (VDDA33), U11.36 (VDDA33), U13.1 (VCC), U37.1 (VIO), U45.24 (VCC), U46.24 (VCC), U54.9 (VDD), U55.5 (VDDIO), U55.8 (VDD), U56.6 (VDDIO), U56.8 (VDD), U59.8 (V+), U60.8 (V+), U61.8 (V+), U62.8 (V+), U66.8 (V+)
ESP_5v: C93.1, C94.1, C95.1, CT4.1, J15.48, J15.49, J28.1, J28.2, J28.3, J28.4, J28.5, J28.6, J28.7, J28.8, R75.1, U37.3 (VDD5), U37.9 (VBUS), U45.1 (A0), U54.15 (A0)
GND: BT1.2 (-), C1.2, C2.2, C3.2, C4.2, C5.2, C6.2, C7.2, C8.2, C9.2, C10.2, C11.2, C12.2, C13.1, C14.2, C15.2, C16.2, C17.2, C18.2, C19.2, C20.2, C21.2, C39.1, C42.2, C78.2, C79.2, C80.2, C81.2, C82.2, C83.2, C84.2, C85.2, C86.2, C87.2, C88.2, C89.2, C90.2, C91.2, C92.2, C93.2, C94.2, C95.2, C103.2, C104.2, C105.2, C106.2, C107.2, C108.2, C109.1, C110.2, C111.2, C113.2, C116.2, C117.2, C118.2, C119.2, C120.2, C121.1, C122.2, C124.2, C125.2, C127.2, C128.2, C131.2, C134.2, C135.2, C136.2, C137.2, C138.1, CT1.2, CT2.2, CT3.2, CT4.2, CT6.2, CT7.2, CT8.2, CT9.2, D4.1 (K), DSI1.1, DSI1.4, DSI1.7, DSI1.10, DSI1.13, DSI1.16, DSI1.19, DSI1.MP (Pin_22), DSI2.1, DSI2.4, DSI2.7, DSI2.10, DSI2.13, DSI2.16, DSI2.19, DSI2.MP (Pin_22), DSW2.12, DSW2.13, DSW2.14, DSW2.15, DSW2.16, ESP1.1 (GND), ESP1.40 (GND), ESP1.41 (GND), GPIO1.6, GPIO1.9, GPIO1.14, GPIO1.20, GPIO1.25, GPIO1.30, GPIO1.34, GPIO1.39, I2C_0x70_1.4, I2C_0x70_2.4, I2C_0x70_3.4, I2C_0x70_4.4, I2C_0x70_5.4, I2C_0x70_6.4, I2C_0x70_7.4, I2C_0x70_8.4, I2C_0x71_1.4, I2C_0x71_2.4, I2C_0x71_3.4, I2C_0x71_4.4, I2C_0x71_5.4, I2C_0x71_7.4, I2C_0x71_8.4, I2C_1.4, I2C_2.4, J2.10 (SHIELD), J2.A4 (GND), J2.A7 (DRAIN), J2.B4 (GND), J2.B7 (DRAIN), J3.2 (D2S), J3.5 (D1S), J3.8 (D0S), J3.11 (CKS), J3.17 (GND), J3.SH1 (SH), J3.SH2 (SH), J3.SH3 (SH), J3.SH4 (SH), J4.2 (D2S), J4.5 (D1S), J4.8 (D0S), J4.11 (CKS), J4.17 (GND), J4.SH1 (SH), J4.SH2 (SH), J4.SH3 (SH), J4.SH4 (SH), J5.19 (SHIELD), J5.20 (SHIELD), J6.1 (GND), J6.3 (GND), J6.9 (GND), J6.15 (GND), J6.21 (GND), J6.27 (GND), J6.33 (GND), J6.39 (GND), J6.45 (GND), J6.51 (GND), J6.57 (GND), J6.71 (GND), J6.73 (GND), J6.75 (GND), J6.M1 (GND2230), J6.M2 (GND2242), J6.S1, J6.S2, J7.4 (GND`), J7.8 (GND), J7.MT1, J7.MT2, J7.MT3, J7.MT4, J8.A1 (GND), J8.A12 (GND), J8.B1 (GND), J8.B12 (GND), J8.S1 (SHIELD), J9.A1 (GND), J9.A12 (GND), J9.B1 (GND), J9.B12 (GND), J9.S1 (SHIELD), J10.A1 (GND), J10.A12 (GND), J10.B1 (GND), J10.B12 (GND), J10.S1 (SHIELD), J12.3, J15.1, J15.8, J15.13, J15.33, J15.34, J15.35, J15.44, J15.45, J15.46, J15.47, J15.57, J15.58, J15.59, J15.60, J15.MP (MountPin), JI2C_0x71_6.4, Module1.1 (GND), Module1.2 (GND), Module1.7 (GND), Module1.8 (GND), Module1.13 (GND), Module1.14 (GND), Module1.22 (GND), Module1.23 (GND), Module1.32 (GND), Module1.33 (GND), Module1.42 (GND), Module1.43 (GND), Module1.52 (GND), Module1.53 (GND), Module1.59 (GND), Module1.60 (GND), Module1.65 (GND), Module1.66 (GND), Module1.71 (GND), Module1.74 (GND), Module1.98 (GND), Module1.107 (GND), Module1.108 (GND), Module1.113 (GND), Module1.114 (GND), Module1.119 (GND), Module1.120 (GND), Module1.125 (GND), Module1.126 (GND), Module1.131 (GND), Module1.132 (GND), Module1.137 (GND), Module1.138 (GND), Module1.144 (GND), Module1.150 (GND), Module1.155 (GND), Module1.156 (GND), Module1.161 (GND), Module1.162 (GND), Module1.167 (GND), Module1.168 (GND), Module1.173 (GND), Module1.174 (GND), Module1.179 (GND), Module1.180 (GND), Module1.185 (GND), Module1.186 (GND), Module1.191 (GND), Module1.192 (GND), Module1.197 (GND), Module1.198 (GND), R1.2, R5.2, R6.2, R7.2, R16.2, R19.2, R20.2, R21.2, R22.1, R23.1, R24.1, R25.2, R26.2, R27.2, R29.1, R30.1, R31.1, R32.1, R104.1, R105.1, R111.1, R112.1, R113.1, R114.1, R119.2, R120.1, SPI1.6, SPI2.6, SPI3.6, SPI4.6, SW1.2, TP3.1, U1.2 (GND), U2.3 (GND), U3.3 (GND), U4.3 (GND), U4.8 (GND), U5.3 (GND), U5.8 (GND), U7.2 (GND), U8.5 (GND), U8.10 (nOE), U9.2 (GND), U10.3 (GND), U10.8 (GND), U11.37 (VSS), U13.5 (GND), U13.10 (nOE), U14.3 (GND), U14.8 (GND), U32.2 (GND), U37.2 (GND), U37.17 (GND), U45.2 (A1), U45.12 (GND), U45.21 (A2), U46.1 (A0), U46.2 (A1), U46.12 (GND), U46.21 (A2), U47.9 (DGND), U47.14 (AGND), U54.10 (VSS), U54.16 (A1), U54.17 (A2), U55.6 (GND), U56.1 (GND), U56.7 (GND), U57.2 (GND), U57.10 (CLKSEL0), U57.11 (NRST), U57.25 (GNDIO), U58.3 (Vss), U59.3 (GND), U60.3 (GND), U61.3 (GND), U62.3 (GND), U64.6 (DGND), U64.11 (ZGND), U64.12 (AGNDL), U64.17 (AGNDR), U64.19 (PGND), U65.7 (GND), U65.9 (GND), U66.3 (GND)
H_EN: J15.22, U54.21 (GPA0)
I2C_CH: DSW2.7, ESP1.31 (IO38), R120.2, U66.1 (IN1), U66.5 (IN2)
I2C_RST: J15.21, R75.2, U45.3 (~RESET), U46.3 (~RESET), U54.22 (GPA1)
INA226_ALERT: ESP1.18 (IO10), J15.32
INA226_SCL: GPIO1.29, J15.12, Module1.34 (GPIO5)
INA226_SDA: GPIO1.7, J15.11, Module1.54 (GPIO4)
MCP_CS: J15.24, U54.11 (~CS), U61.6 (COM2)
unnamed: C7.1, J5.4 (CT), J5.5 (CT)
unnamed: C123.2, R111.2
unnamed: C126.2, R112.2
unnamed: C129.2, C132.2, R113.2
unnamed: C130.2, C133.2, R114.2
unnamed: C132.1, R115.1
unnamed: C133.1, R116.1
unnamed: D1.1 (K), R8.1
unnamed: D2.1 (K), R9.1
unnamed: D3.1 (K), R15.1
unnamed: D4.2 (A), R69.1
unnamed: D5.2 (A), R70.1
unnamed: D6.2 (A), R71.1
unnamed: D16.2 (A), R11.2
unnamed: D16.1 (K), R10.2, U32.3 (FLG)
unnamed: DSI2.17, R2.2
unnamed: DSW2.9, R5.1
unnamed: DSW2.10, R6.1
unnamed: DSW2.11, R7.1
unnamed: J5.18 (LEDG_K), R13.1
unnamed: J5.16 (LEDY_K), R12.1
unnamed: J6.10 (DAS/~DSS/~LED1), R15.2
unnamed: J6.68 (SUSCLK), U7.3 (Out)
unnamed: J8.A5 (CC1), R23.2
unnamed: J8.B5 (CC2), R24.2
unnamed: J10.A5 (CC1), R30.2
unnamed: J10.B5 (CC2), R32.2
unnamed: J10.A4 (VBUS), J10.A9 (VBUS), J10.B4 (VBUS), J10.B9 (VBUS), R28.1
unnamed: J17.1, R156.2
unnamed: J17.2, U47.2 (CH1)
unnamed: J18.1, R157.2
unnamed: J18.2, U47.3 (CH2)
unnamed: J21.1, R155.2
unnamed: J21.2, U47.1 (CH0)
unnamed: J22.1, R158.2
unnamed: J22.2, U47.4 (CH3)
unnamed: J23.1, R101.2
unnamed: J23.2, U47.5 (CH4)
unnamed: J24.1, R102.2
unnamed: J24.2, U47.6 (CH5)
unnamed: Module1.21 (LED_nACT), R8.2
unnamed: Q2.1 (B), R74.1
unnamed: Q2.2 (E), R73.1, U37.12 (DTR)
unnamed: Q3.1 (B), R73.2
unnamed: Q3.2 (E), R74.2, U37.13 (RTS)
unnamed: R9.2, U3.4
unnamed: R118.2, SPEAKER1.1, U65.8 (V_{O-})
unnamed: R117.2, SPEAKER1.2, U65.5 (V_{O+})
unnamed: R1.1, U1.5 (ILIM)
unnamed: R26.1, U9.5 (ILIM)
unnamed: R25.1, U11.25 (HS_IND/CFG_SEL1)
unnamed: R22.2, U11.35 (RBIAS)
unnamed: R18.2, U11.26 (RESET_N)
unnamed: R19.1, U11.24 (SCL/SMBCLK/CFG_SEL0)
unnamed: R20.1, U11.22 (SDA/SMBDATA/NON_REM1)
unnamed: R21.1, U11.28 (SUSP_IND/LOCAL_PWR/NON_REM0)
unnamed: C12.1, U11.33 (XTALIN/CLKIN), Y1.1
unnamed: C14.1, U11.32 (XTALOUT), Y1.2
unnamed: U12.3 (GND), U12.8 (GND)
unnamed: J10.A7 (D-), J10.B7 (D-), U13.8 (HSD1_M), U14.2 (D1-), U14.9
unnamed: J10.A6 (D+), J10.B6 (D+), U13.9 (HSD1_P), U14.1 (D1+), U14.10
unnamed: R27.1, R28.2, U13.2 (SEL)
unnamed: C84.1, U37.6 (V3)
unnamed: C39.2, C42.1, U47.15 (Vref), U58.2 (Vout)
unnamed: R108.2, U64.9 (D+)
unnamed: R109.2, U64.8 (D-)
unnamed: R106.1, U64.3 (DT)
unnamed: SW2.2, U64.22 (HID0/MS)
unnamed: SW3.2, U64.23 (HID1/MC)
unnamed: SW4.2, U64.24 (HID2/MD)
unnamed: C128.1, U64.13 (VCCL)
unnamed: C127.1, U64.20 (VCCP)
unnamed: C125.1, U64.16 (VCCR)
unnamed: C131.1, U64.18 (VCOM)
unnamed: C126.1, C129.1, U64.14 (VOUTL)
unnamed: C123.1, C130.1, U64.15 (VOUTR)
unnamed: C122.1, R110.2, U64.28 (XTI), Y3.2
unnamed: C120.1, R110.1, U64.1 (XTO), Y3.1
unnamed: SW2.1, SW3.1, SW4.1, U64.27 (~SSPND)
unnamed: R116.2, R118.1, U65.3 (IN+)
unnamed: R115.2, R117.1, U65.4 (IN-)
PD-CHARGE_CC1: J9.A5 (CC1), R29.2
PD-CHARGE_CC2: J9.B5 (CC2), R31.2
PD-CHARGE_VBUS: J9.A4 (VBUS), J9.A9 (VBUS), J9.B4 (VBUS), J9.B9 (VBUS)
PMIC_ENABLE: DSW2.5, Module1.99 (PMIC_ENABLE)
RPI_5V: GPIO1.2, GPIO1.4, J12.1, J15.50, J15.51, J15.52, J15.53, J15.54, Module1.77 (+5v_(Input)), Module1.79 (+5v_(Input)), Module1.81 (+5v_(Input)), Module1.83 (+5v_(Input)), Module1.85 (+5v_(Input)), Module1.87 (+5v_(Input))
SEN_SCL: GPIO1.26, Module1.37 (GPIO7), U66.4 (NO2)
SEN_SDA: GPIO1.31, Module1.30 (GPIO6), U66.2 (NO1)
SPI0_CLK: GPIO1.23, Module1.38 (GPIO11), U61.2 (NO1)
SPI0_CS: GPIO1.24, Module1.39 (GPIO8), U61.4 (NO2)
SPI0_MISO: GPIO1.21, Module1.40 (GPIO9), U62.4 (NO2)
SPI0_MOSI: GPIO1.19, Module1.44 (GPIO10), U62.2 (NO1)
SPI1_CLK: GPIO1.40, Module1.25 (GPIO21), U59.2 (NO1)
SPI1_MISO: GPIO1.35, Module1.26 (GPIO19), U60.4 (NO2)
SPI1_MOSI: GPIO1.38, Module1.27 (GPIO20), U60.2 (NO1)
SPI2_CH: ESP1.33 (MTDO/IO40), R105.2, U61.1 (IN1), U61.5 (IN2), U62.1 (IN1), U62.5 (IN2)
SPI_TMC_CH: DSW2.8, ESP1.32 (MTCK/IO39), R104.2, U59.1 (IN1), U59.5 (IN2), U60.1 (IN1), U60.5 (IN2)
TPA_ON: J15.23, R119.1, U65.1 (~SHUTDOWN)
Uart_rx: ESP1.11 (IO18), GPIO1.8, Module1.55 (GPIO14)
Uart_tx: ESP1.10 (IO17), GPIO1.10, Module1.51 (GPIO15)
WL_nDis: DSW2.2, Module1.89 (WiFi_nDisable)
WS_2802B_DATA: ESP1.23 (IO21), J15.25
nRPIBOOT: DSW2.4, Module1.93 (nRPIBOOT)

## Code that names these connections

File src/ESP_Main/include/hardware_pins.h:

#pragma once
#include <Arduino.h>

//ESP GPIO pins
const int DM_A0pin = 4;
const int DM_A1pin = 5;
const int DM_A2pin = 6;
const int DM_A3pin = 7;
//Sensor SPI bus
const int Sensor_SPI_MOSI = 38;
const int Sensor_SPI_MISO = 39;
const int Sensor_SPI_CS = 40;
const int Sensor_SPI_SCL = 41;


//for testing
const int BNO_INT = 36;
const int BNO_RST = 35;
const uint8_t TMC_EN = 21;
const uint8_t BME280_CS = 45;


const uint8_t Servo1_pin = 20;




// << ======= >>
// Demultilexer pins
const int DM_ICM_CS = 0; // ICM Gyro-Sensor
const int DM_BNO_CS = 1; // BNO IMU Modul
const int DM_BME280_CS = 2; // BME280 Temperature, Huminydi and pressure sensor
const int DM_AD_MCP_CS = 3; // AD Mcp is a Analog-Digital converter for 10k ntcs
const int DM_SPI1_CS = 4; // SPI Connector 1 Chip Sellect
const int DM_SPI2_CS = 5; // SPI Connector 2 Cship Select
const int DM_SPI3_CS = 6; // SPI Connector 3 Cship Select
const int DM_SPI4_CS = 7; // SPI Connector 4 Cship Select
const int DM_M1_CS = 8; // Stepper motor 1 Chip Select
const int DM_M2_CS = 9; // Stepper motor 2 Chip Select
const int DM_M3_CS = 10; // Stepper motor 3 Chip Select
const int DM_M4_CS = 11; // Stepper motor 4 Chip Select
const int DM_MCP_CS = 12; // MCP IO Expander Chip Select
const int DM_DIAG_LED1 = 13; // Dignostic Led 1
const int DM_DIAG_LED2 = 14; // Dignostic Led 2
const int DM_DIAG3_LED3 = 15; // Dignostic Led 2 (Also Empty Chanel)

// TMC5160
const float TMC_R_SENSE = 0.075;

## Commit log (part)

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2025-05-22 feat: Initialize project repository
    This is the first commit, establishing the foundational structure of the project. It includes the initial .gitignore file to exclude unnecessary files from version control and a basic README.md to pr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
2025-05-22 docs: Enhance project README.md
    The README.md has been updated to include more comprehensive information about the project's goals, scope, and the technologies being used. This provides better initial documentation for anyone viewi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
2025-05-22 webpage init
2025-05-22 Wemos D1 mini wifi távolságmérő html css segítségével (HC-SR-04)
2025-05-22 feat(sensor): Add HC-SR04 distance sensor with Wi-Fi webpage
    Implements a PlatformIO project for the Wemos D1 Mini to measure distance using an HC-SR-04 ultrasonic sensor. The data is served over Wi-Fi via a web server, which presents the distance on a simple 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
2025-05-22 feat(sensor): Implement dual-channel HC-SR04 measurement
    Adds a new program to read from two HC-SR-04 sensors simultaneously. This commit also restructures the project by creating a top-level 'Sensors' directory to better organize sensor-related code and e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
2025-05-22 feat(sensor): Add RGB rainbow effect for Arduino
    Introduces a new project under 'Sensors/RGB_LED'. This code creates a rainbow color cycle effect on an RGB LED strip connected to an Arduino-compatible board. It serves as a test for controlling addr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
2025-05-22 Media update (RGB, SR-HC-04, L298N)
2025-05-22 docs(media): Add media for various components
    Updates the repository with new media files (images and/or videos) in the 'media' directory. These files document the progress and setup for the RGB LED, HC-SR-04 distance sensor, and the L298N motor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
2025-05-22 L298N motor controller test code
2025-05-22 docs: Add archived ChatGPT conversations for reference
    Adds a 'ChatGPT' directory containing several PDF files. These are saved conversation logs with ChatGPT that provided useful information, code snippets, or debugging help for various project componen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
2025-05-22 First 3D conception
2025-05-22 feat(3d): Add first 3D model concept
    Introduces the first 3D conceptual model for the robot. This includes an initial STL file ('Stepper Flag.stl') located in the 'Robot 3d/basic' directory, likely for testing purposes.
2025-05-26 A4988 motor stepper controller test
2025-05-26 feat(motor): Add A4988 stepper driver test code
    Adds a new test project for controlling a stepper motor using the A4988 driver. This project is created under 'Motor/A4988' and serves to validate the control logic for stepper motors.
2025-05-30 2 mothor with hc-sr04
2025-05-30 2 motor together with HC-SR 04 updated
2025-05-30 new circuit_v0.2
2025-06-02 TMC2209 UART try
2025-06-02 WIP: 2 motor with tmc2209 and VL53L1X
2025-06-02 rms_current reduced
2025-06-02 kicad v0.3 + EV color 0.1
2025-06-15 CJMCU-2812-8 rgb led strip
2025-06-16 web update, kicad saves
2025-06-16 web edited
2025-06-16 LED with color sensor finished (object-oriented)
2025-06-23 altium V0
2025-06-29 circuit and datasheet update
2025-06-29 color recognition final version
2025-07-02 some value changed
2025-07-02 raspi uart with esp32
2025-07-03 camera upgraded to oop
2025-07-07 kicad i2c schematic updated: gyto i2c bugfixes, +add new datasheets
2025-07-07 media update
2025-07-07 kicad bugfixs + bno085 + level shifter ics
2025-07-07 media update with szekér
2025-07-08 pcb update
2025-07-08 full_uart communication_logic first version
2025-07-09 feat(sensor): Add ESP32 test for HC-SR04 and EV3 Color Sensor
    Introduces new experiments: one testing the HC-SR04 sensor with an ESP32 board, and another folder for initial tests with the EV3 Color Sensor. This expands hardware testing capabilities.
2025-07-09 feat(motor): Integrate two motors with HC-SR04 sensor
    Creates a new project that combines two A4988-driven stepper motors with an HC-SR-04 distance sensor. This is the first step towards creating an autonomous, obstacle-avoiding robot base.
2025-07-09 feat(kicad): Create version 0.2 of the main circuit
    Introduces a new iteration of the main robot PCB design, version 0.2. This KiCad project, located in 'Circuit/kicad/robot_v2', represents a significant update to the electronic design.
2025-07-09 docs(media): Add media for dual motor and HC-SR04 setup
    Adds new media files (images/videos) showcasing the integrated system of two stepper motors controlled by A4988 drivers and the HC-SR04 sensor in action.
2025-07-09 refactor(motor): Update dual motor and HC-SR04 integration
    Refines the code for the two-motor setup with the HC-SR04 sensor. This update likely improves the control logic, coordination between movement and sensing, or general code structure.
2025-07-09 feat(sensor): Add initial test for VL53L1X ToF sensor
    Adds a test program for the VL53L1X Time-of-Flight distance sensor. This provides a more accurate and faster alternative to the HC-SR04 ultrasonic sensor for distance measurements.
2025-07-09 feat(sensor): Add initial test for TCS34725 color sensor
    Adds a PlatformIO project to test the TCS34725 color sensor. This enables the robot to detect and differentiate colors, opening up new possibilities for interaction with its environment.
2025-07-09 feat(motor): WIP integration of TMC2209 and VL53L1X
    Work-in-progress on a new project to combine two motors driven by TMC2209 drivers with the VL53L1X distance sensor. This aims to create a more advanced robot base with precise motor control and sensi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
2025-07-09 refactor(web): Edit and refine project webpage
    Further edits and improvements have been made to the project's webpage. This could include content updates, style changes, or structural enhancements to the HTML.
2025-07-09 feat(sensor): Create project for RGB LEDs with color sensor
    Initiates a new project to integrate the TCS34725 color sensor with the CJMCU-2812-8 RGB LED strip. The goal is for the LEDs to reflect the color detected by the sensor.
2025-07-09 chore: Update web page and save KiCad progress
    This commit includes miscellaneous updates. The project's webpage (`web/index.html`) has been modified, and various KiCad project files have been saved, reflecting ongoing design work.
2025-07-09 feat(camera): Add OpenCV color recognition script
    Introduces a Python script using the OpenCV library for camera-based color recognition. This script, located in `Camera/`, is the first step towards implementing computer vision capabilities.
2025-07-09 refactor(sensor): Finalize color sensor and LED project with OOP
    Completes the project integrating the color sensor and RGB LEDs. The code has been refactored into an object-oriented structure, using classes for the ColorSensor and LED components for better organi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
2025-07-09 refactor(camera): Finalize color recognition script
    Completes and refines the camera-based color recognition script. This 'final version' likely includes improved accuracy, better structure, and more robust color detection logic.
2025-07-09 feat(robot): Implement first integrated robot movements
    This commit marks a significant milestone with the first successful movements of the integrated robot prototype. It combines motors, sensors, and control logic to achieve basic motion.
2025-07-09 feat(comm): Establish UART communication between Raspberry Pi and ESP32
    Implements the initial code for establishing a serial (UART) communication link between a Raspberry Pi and an ESP32. This is crucial for the high-level/low-level control architecture.
2025-07-09 refactor(camera): Refine center-screen color detection logic
    This commit adjusts the color detection algorithm in the OpenCV script. To improve stability and reduce sensitivity to sensor noise, the method was changed from reading a single pixel to analyzing a 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
2025-07-09 feat(comm): Implement first communication program for v1 model
    Develops the first version of the main communication program for the 'v1.0' robot model. This likely defines the initial protocol and logic for commands exchanged between the main processor and micro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
2025-07-09 docs: Update circuit diagrams and datasheets
    This commit updates the electronic design documentation. It includes changes to the KiCad/Altium circuit files and adds new or updated component datasheets to the 'Datasheets' directory.
2025-07-09 docs(media): Update media gallery with new content
    Adds new images and videos to the 'media' directory to document recent progress, showcase new features, or provide updated views of the robot's hardware.
2025-07-09 fix(kicad): Correct I2C schematic and add new datasheets
    This commit resolves bugs in the I2C bus wiring on the main PCB schematic. It also expands the project's documentation by adding several new component datasheets.
2025-07-09 feat(kicad): Add BNO085 IMU and level shifters to PCB
    Updates the KiCad schematic and layout to include a BNO085 9-DOF IMU for orientation sensing. Also adds I2C level shifter ICs to ensure compatibility between 5V and 3.3V components and fixes related 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
2025-07-09 docs: Update PCB files and datasheets
    This commit includes general updates to the PCB design files (KiCad/Altium) and adds or revises datasheets in the documentation folder.
2025-07-09 refactor(kicad): Perform significant PCB update
    This commit contains a substantial update to the main PCB layout in KiCad. Changes likely include major rerouting, component repositioning, or adding new circuit blocks.
2025-07-09 refactor(kicad): Clean up PCB v3.01 and add robot chassis 3D model
    Finalizes and cleans up version 3.01 of the main KiCad PCB, tidying up schematics and layout. Also adds the 3D model files for the v0.1 robot chassis to the 'Robot 3d' directory.
2025-07-09 feat(comm): Implement first version of UART logic
    This commit adds the initial, self-contained version of the UART communication logic. This serves as a foundational block for the more complex, fully-integrated communication protocol.
2025-07-09 chore(kicad): Update KiCad project files
    Saves ongoing work on the KiCad project. This commit includes incremental changes and updates to the schematic and/or PCB layout.
2025-07-09 refactor(comm): Refine and enhance UART LED control logic
    This commit improves upon the previously implemented UART LED control system. The logic has been refined for greater reliability and responsiveness, addressing shortcomings of the initial version and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
2025-07-10 robot starts on touch
2025-07-10 Two shift registers together
2025-07-10 M.2 power rail fixed
2025-07-10 Kicad update: power rails v1.0, todo: hc-sr-04 as6500 ic review shift registers change to MCP23S17_SO
2025-07-11 Uart logic v2 finished
2025-07-11 kicad v0.1 footprint- assing spi finish
2025-07-12 kicad update new readme media updates the circuit is 95% finished
2025-07-13 readme updated kicad circuit V1
2025-07-14 TCA9548A and AS7341
2025-07-14 BNO08x_SPI
2025-07-15 MPL3115A2 + web folder deleted
2025-07-15 VL53L0X + Accel stepper extras folder deleted
2025-07-21 Gyro sensor OOP + gyro callibration added
2025-07-22 oop color sensor added
2025-08-01 TMC5160_SPI
2025-08-20 updated kicad (big_update)
2025-08-21 kicad final circuit 1
2025-08-21 kicad final v2
2025-08-23 kicad update (first try pcb, added JB leds, rename i2c headers footprint)
2025-08-25 KiCAD PCB-INA
2025-08-28 TMC full SPI mode
2025-08-29 RPI+ESP SPI communication crc
2025-08-30 RCWL_1601 I2C
2025-09-02 SPI communication working
2025-09-07 new 2 pcb schematics in v4.0 folder, psu sch finish, bad pcb, high speed: bad pcb and sch
2025-09-08 kicad v4 psu pcb clean
2025-09-08 the code is object-oriented
2025-09-11 Main program SPIbus 2
2025-09-15 kicad psu pcb finish psu
2025-09-16 kicad FINISH PSU PCB
2025-09-16 kicad pcb soldermask update
2025-10-01 PSU bugfixes
2025-10-06 V4.1.7 PSU V1.0 debug Card
2025-10-16 high speed first step
2025-10-18 high speed update
2025-10-22 kicad
2025-10-24 FINISH PSU V1.4.9 to production 1
2025-11-27 finished high-speed panel schematic and first try to doute gpios
2025-11-28 Main program Demux Finished
2025-11-30 BNO085 main code
2025-12-02 TMC5160 with demultiplexer
2025-12-02 TMC5160 init bug fixing
2025-12-04 ForwardCMWitGyro tested and BME28 class created
2025-12-04 ICM45686 library added
2025-12-15 high speed nev diff v1
2025-12-15 kicad gyártás
2026-04-22 the mooving functions are finished
